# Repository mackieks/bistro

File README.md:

# bistro
Wii U regulator board. Runs a Wii U motherboard (no disc drive) from 1S lithium-ion. Licensed under Solderpad Hardware License v2.1. Have fun!

- x2 SiC431C 24A buck regulators for 1v and 1.15v (CPU + GPU)
- x2 MUN3CAD01-SB 1A bucks for 1.1V and 1.25V (for DRH)
- x1 MUN3CAD03-SE 3A buck for 1.5V (RAM)
- x1 TPS63810YFFR 2.5A buck-boost for 3.3V
- x1 FAN48610BUC50X 5V 1A boost (USB)

[Mouser project with BOM](https://www.mouser.com/ProjectManager/ProjectDetail.aspx?AccessID=d68b6111f5)

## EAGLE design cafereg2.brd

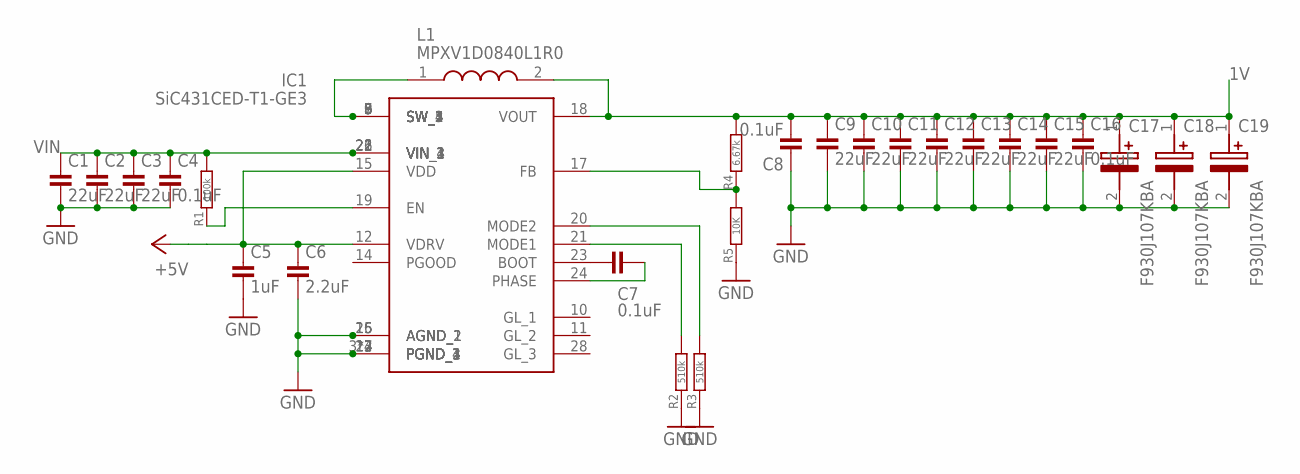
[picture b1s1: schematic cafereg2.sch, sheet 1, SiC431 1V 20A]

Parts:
C1, C2, C3, C9, C10, C11, C12, C13, C14, C15: 22uF; C0603
C4, C7, C8, C16: 0.1uF; C0402
C5: 1uF; C0402
C6: 2.2uF; C0402
C17, C18, C19: F930J107KBA; CAPPM3528X210N
IC1: SiC431CED-T1-GE3; SIC431AEDT1GE3
L1: MPXV1D0840L1R0; INDPM8680X400N
R1: 100k; R0402
R2, R3: 510k; R0402
R4: 6.67k; R0402
R5: 10K; R0402

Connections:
1V: C8.2, C9.1, C10.1, C11.1, C12.1, C13.1, C14.1, C15.1, C16.1, C17.1 (+), C18.1 (+), C19.1 (+), IC1.18 (VOUT), L1.2, R4.2
+5V: C5.1, C6.1, IC1.12 (VDRV), IC1.15 (VDD); also elsewhere on the board
BOOT: C7.1, IC1.23 (BOOT)
FB: IC1.17 (FB), R4.1, R5.2
GND: C1.2, C2.2, C3.2, C4.2, C5.2, C6.2, C8.1, C9.2, C10.2, C11.2, C12.2, C13.2, C14.2, C15.2, C16.2, C17.2 (-), C18.2 (-), C19.2 (-), IC1.3 (PGND_1), IC1.4 (PGND_2), IC1.13 (PGND_3), IC1.16 (AGND_1), IC1.25 (AGND_2), IC1.27 (PGND_4), IC1.29 (PGND_1), R2.1, R3.1, R5.1; also elsewhere on the board
unnamed: IC1.19 (EN), R1.1
unnamed: IC1.21 (MODE1), R2.2
unnamed: IC1.5 (SW_1), IC1.6 (SW_2), IC1.7 (SW_3), IC1.8 (SW_4), IC1.9 (SW_5), L1.1
unnamed: IC1.20 (MODE2), R3.2
PHASE: C7.2, IC1.24 (PHASE)
VIN: C1.1, C2.1, C3.1, C4.1, IC1.1 (VIN_1), IC1.2 (VIN_2), IC1.22 (VIN_3), IC1.26 (VIN_4), R1.2; also elsewhere on the board

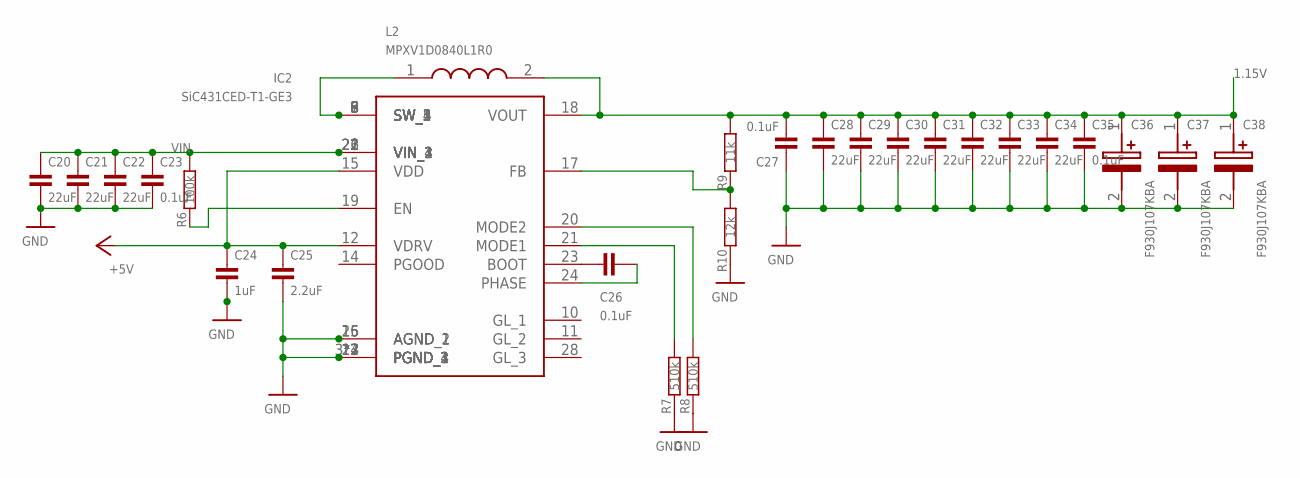
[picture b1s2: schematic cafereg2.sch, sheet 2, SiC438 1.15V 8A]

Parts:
C20, C21, C22, C28, C29, C30, C31, C32, C33, C34: 22uF; C0603
C23, C26, C27, C35: 0.1uF; C0402
C24: 1uF; C0402
C25: 2.2uF; C0402
C36, C37, C38: F930J107KBA; CAPPM3528X210N
IC2: SiC431CED-T1-GE3; SIC431AEDT1GE3
L2: MPXV1D0840L1R0; INDPM8680X400N
R6: 100k; R0402
R7, R8: 510k; R0402
R9: 11k; R0402
R10: 12k; R0402

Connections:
1.15V: C27.2, C28.1, C29.1, C30.1, C31.1, C32.1, C33.1, C34.1, C35.1, C36.1 (+), C37.1 (+), C38.1 (+), IC2.18 (VOUT), L2.2, R9.2
+5V: C24.1, C25.1, IC2.12 (VDRV), IC2.15 (VDD); also elsewhere on the board
BOOT2: C26.1, IC2.23 (BOOT)
FB2: IC2.17 (FB), R9.1, R10.2
GND: C20.2, C21.2, C22.2, C23.2, C24.2, C25.2, C27.1, C28.2, C29.2, C30.2, C31.2, C32.2, C33.2, C34.2, C35.2, C36.2 (-), C37.2 (-), C38.2 (-), IC2.3 (PGND_1), IC2.4 (PGND_2), IC2.13 (PGND_3), IC2.16 (AGND_1), IC2.25 (AGND_2), IC2.27 (PGND_4), IC2.29 (PGND_1), R7.1, R8.1, R10.1; also elsewhere on the board
unnamed: IC2.19 (EN), R6.1
unnamed: IC2.5 (SW_1), IC2.6 (SW_2), IC2.7 (SW_3), IC2.8 (SW_4), IC2.9 (SW_5), L2.1
unnamed: IC2.21 (MODE1), R7.2
unnamed: IC2.20 (MODE2), R8.2
PHASE2: C26.2, IC2.24 (PHASE)
VIN: C20.1, C21.1, C22.1, C23.1, IC2.1 (VIN_1), IC2.2 (VIN_2), IC2.22 (VIN_3), IC2.26 (VIN_4), R6.2; also elsewhere on the board

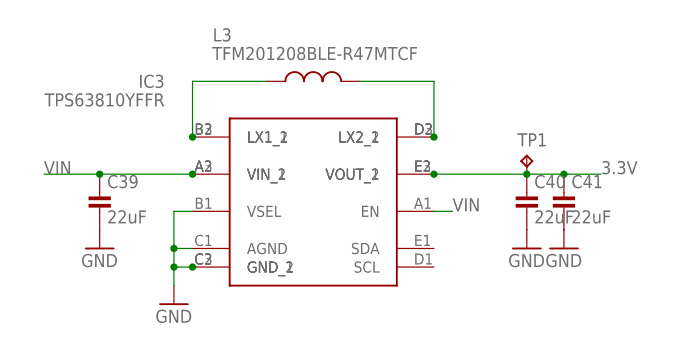
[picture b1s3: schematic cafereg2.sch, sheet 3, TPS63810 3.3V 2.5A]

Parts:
C39, C40, C41: 22uF; C0603
IC3: TPS63810YFFR; BGA15C40P3X5_134X226X62
L3: TFM201208BLE-R47MTCF; INDC2009X120
TP1: TPTP12SQ; TP12SQ

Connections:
3.3V: C40.1, C41.1, IC3.E2 (VOUT_1), IC3.E3 (VOUT_2), TP1.TP
GND: C39.2, C40.2, C41.2, IC3.B1 (VSEL), IC3.C1 (AGND), IC3.C2 (GND_1), IC3.C3 (GND_2); also elsewhere on the board
SW1: IC3.B2 (LX1_1), IC3.B3 (LX1_2), L3.1
SW2: IC3.D2 (LX2_1), IC3.D3 (LX2_2), L3.2
VIN: C39.1, IC3.A1 (EN), IC3.A2 (VIN_1), IC3.A3 (VIN_2); also elsewhere on the board

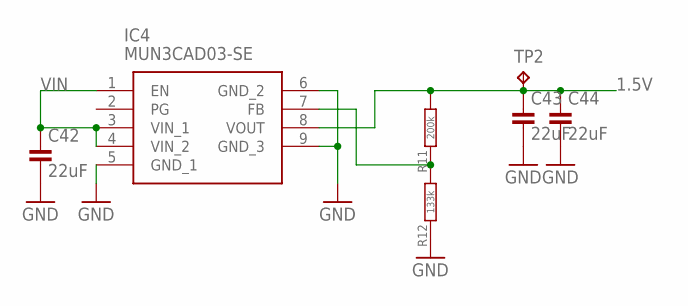
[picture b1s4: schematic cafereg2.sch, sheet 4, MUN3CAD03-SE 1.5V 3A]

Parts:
C42, C43, C44: 22uF; C0603
IC4: MUN3CAD03-SE; MUN3CAD03SE
R11: 200k; R0402
R12: 133k; R0402
TP2: TPTP12SQ; TP12SQ

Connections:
1.5V: C43.1, C44.1, IC4.8 (VOUT), R11.2, TP2.TP
FB1: IC4.7 (FB), R11.1, R12.2
GND: C42.2, C43.2, C44.2, IC4.5 (GND_1), IC4.6 (GND_2), IC4.9 (GND_3), R12.1; also elsewhere on the board
VIN: C42.1, IC4.1 (EN), IC4.3 (VIN_1), IC4.4 (VIN_2); also elsewhere on the board

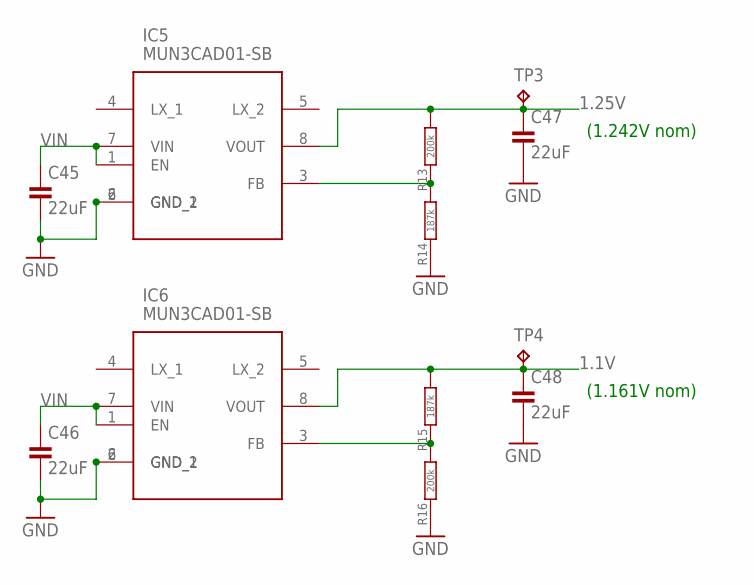
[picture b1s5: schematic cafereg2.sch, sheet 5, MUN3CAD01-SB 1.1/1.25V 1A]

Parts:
C45, C46, C47, C48: 22uF; C0603
IC5, IC6: MUN3CAD01-SB; MUN3CAD01SB
R13, R16: 200k; R0402
R14, R15: 187k; R0402
TP3, TP4: TPTP12SQ; TP12SQ

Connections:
1.1V: C48.1, IC6.8 (VOUT), R15.2, TP4.TP
1.25V: C47.1, IC5.8 (VOUT), R13.2, TP3.TP
GND: C45.2, C46.2, C47.2, C48.2, IC5.2 (GND_1), IC5.6 (GND_2), IC6.2 (GND_1), IC6.6 (GND_2), R14.1, R16.1; also elsewhere on the board
unnamed: IC6.3 (FB), R15.1, R16.2
unnamed: IC5.3 (FB), R13.1, R14.2
VIN: C45.1, C46.1, IC5.1 (EN), IC5.7 (VIN), IC6.1 (EN), IC6.7 (VIN); also elsewhere on the board

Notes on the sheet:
(1.161V nom)
(1.242V nom)

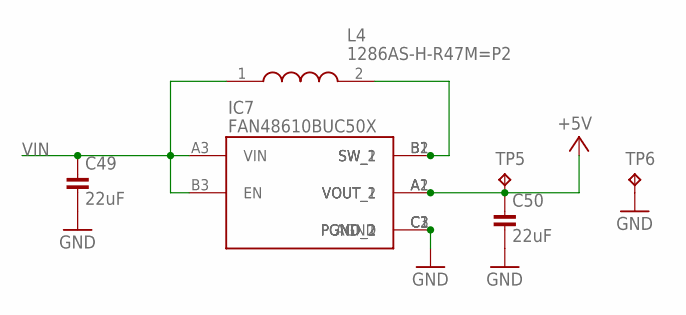
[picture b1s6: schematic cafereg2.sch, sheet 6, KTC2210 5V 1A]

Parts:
C49, C50: 22uF; C0603
IC7: FAN48610BUC50X; BGA9C40P3X3_122X122X62
L4: 1286AS-H-R47M=P2; 1286ASH1R0MP2
TP5, TP6: TPTP12SQ; TP12SQ

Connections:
+5V: C50.1, IC7.A1 (VOUT_1), IC7.A2 (VOUT_2), TP5.TP; also elsewhere on the board
GND: C49.2, C50.2, IC7.C1 (PGND_1), IC7.C2 (PGND_2), IC7.C3 (AGND), TP6.TP; also elsewhere on the board
SW: IC7.B1 (SW_1), IC7.B2 (SW_2), L4.2
VIN: C49.1, IC7.A3 (VIN), IC7.B3 (EN), L4.1; also elsewhere on the board

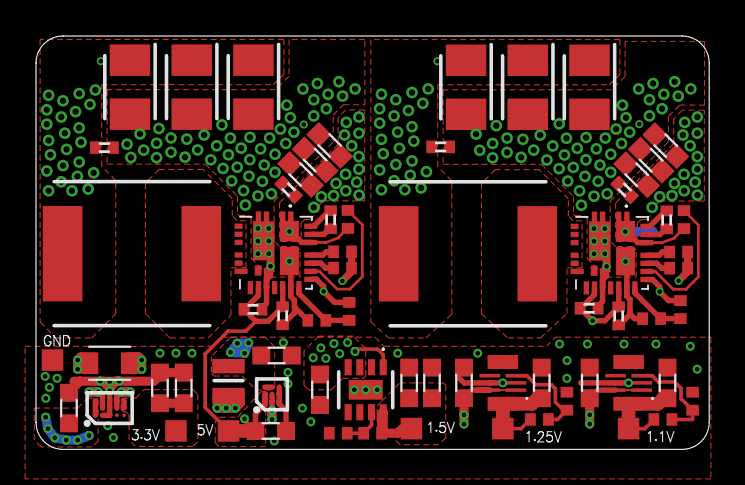
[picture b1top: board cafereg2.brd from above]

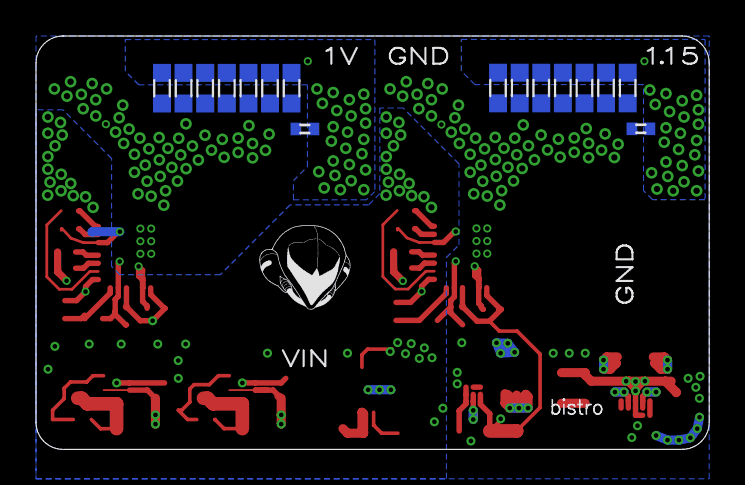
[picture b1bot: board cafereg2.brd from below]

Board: 4 copper layers, 37.4 x 23.0 mm, 83 parts (16 on the bottom side), 29 nets.

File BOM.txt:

Partlist

Exported from cafereg2.sch at 12/10/2023 4:18 PM

EAGLE Version 9.6.1 Copyright (c) 1988-2020 Autodesk, Inc.

Assembly variant: 

Part     Value                Device                   Package                 Library        Sheet

C1       22uF                 C-USC0603                C0603                   resistor       1
C2       22uF                 C-USC0603                C0603                   resistor       1
C3       22uF                 C-USC0603                C0603                   resistor       1
C4       0.1uF                C-USC0402                C0402                   resistor       1
C5       1uF                  C-USC0402                C0402                   resistor       1
C6       2.2uF                C-USC0402                C0402                   resistor       1
C7       0.1uF                C-USC0402                C0402                   resistor       1
C8       0.1uF                C-USC0402                C0402                   resistor       1
C9       22uF                 C-USC0603                C0603                   resistor       1
C10      22uF                 C-USC0603                C0603                   resistor       1
C11      22uF                 C-USC0603                C0603                   resistor       1
C12      22uF                 C-USC0603                C0603                   resistor       1
C13      22uF                 C-USC0603                C0603                   resistor       1
C14      22uF                 C-USC0603                C0603                   resistor       1
C15      22uF                 C-USC0603                C0603                   resistor       1
C16      0.1uF                C-USC0402                C0402                   resistor       1
C17      F930J107KBA          F930J107KBA              CAPPM3528X210N          SamacSys_Parts 1
C18      F930J107KBA          F930J107KBA              CAPPM3528X210N          SamacSys_Parts 1
C19      F930J107KBA          F930J107KBA              CAPPM3528X210N          SamacSys_Parts 1
C20      22uF                 C-USC0603                C0603                   resistor       2
C21      22uF                 C-USC0603                C0603                   resistor       2
C22      22uF                 C-USC0603                C0603                   resistor       2
C23      0.1uF                C-USC0402                C0402                   resistor       2
C24      1uF                  C-USC0402                C0402                   resistor       2
C25      2.2uF                C-USC0402                C0402                   resistor       2
C26      0.1uF                C-USC0402                C0402                   resistor       2
C27      0.1uF                C-USC0402                C0402                   resistor       2
C28      22uF                 C-USC0603                C0603                   resistor       2
C29      22uF                 C-USC0603                C0603                   resistor       2
C30      22uF                 C-USC0603                C0603                   resistor       2
C31      22uF                 C-USC0603                C0603                   resistor       2
C32      22uF                 C-USC0603                C0603                   resistor       2
C33      22uF                 C-USC0603                C0603                   resistor       2
C34      22uF                 C-USC0603                C0603                   resistor       2
C35      0.1uF                C-USC0402                C0402                   resistor       2
C36      F930J107KBA          F930J107KBA              CAPPM3528X210N          SamacSys_Parts 2
C37      F930J107KBA          F930J107KBA              CAPPM3528X210N          SamacSys_Parts 2
C38      F930J107KBA          F930J107KBA              CAPPM3528X210N          SamacSys_Parts 2
C39      22uF                 C-USC0603                C0603                   resistor       3
C40      22uF                 C-USC0603                C0603                   resistor       3
C41      22uF                 C-USC0603                C0603                   resistor       3
C42      22uF                 C-USC0603                C0603                   resistor       4
C43      22uF                 C-USC0603                C0603                   resistor       4
C44      22uF                 C-USC0603                C0603                   resistor       4
C45      22uF                 C-USC0603                C0603                   resistor       5
C46      22uF                 C-USC0603                C0603                   resistor       5
C47      22uF                 C-USC0603                C0603                   resistor       5
C48      22uF                 C-USC0603                C0603                   resistor       5
C49      22uF                 C-USC0603                C0603                   resistor       6
C50      22uF                 C-USC0603                C0603                   resistor       6
IC1      SiC431CED-T1-GE3     SiC431CED-T1-GE3         SiC431CED-T1-GE3        personal       1
IC2      SiC431CED-T1-GE3     SiC431CED-T1-GE3         SiC431CED-T1-GE3        personal       2
IC3      TPS63810YFFR         TPS63810YFFR             BGA15C40P3X5_134X226X62 SamacSys_Parts 3
IC4      MUN3CAD03-SE         MUN3CAD03-SE             MUN3CAD03SE             SamacSys_Parts 4
IC5      MUN3CAD01-SB         MUN3CAD01-SB             MUN3CAD01SB             SamacSys_Parts 5
IC6      MUN3CAD01-SB         MUN3CAD01-SB             MUN3CAD01SB             SamacSys_Parts 5
IC7      FAN48610BUC50X       FAN48610BUC50X           BGA9C40P3X3_122X122X62  SamacSys_Parts 6
L1       MPXV1D0840L1R0       MPXV1D0840L1R0           INDPM8680X400N          SamacSys_Parts 1
L2       MPXV1D0840L1R0       MPXV1D0840L1R0           INDPM8680X400N          SamacSys_Parts 2
L3       TFM201208BLE-R47MTCF L_CHIP-0805(2012-METRIC) INDC2009X120            Inductor       3
L4       1286AS-H-R47M=P2     1286AS-H-R47M=P2         1286ASH1R0MP2           SamacSys_Parts 6
R1       100k                 R-US_R0402               R0402                   resistor       1
R2       510k                 R-US_R0402               R0402                   resistor       1
R3       510k                 R-US_R0402               R0402                   resistor       1
R4       6.67k                R-US_R0402               R0402                   resistor       1
R5       10K                  R-US_R0402               R0402                   resistor       1
R6       100k                 R-US_R0402               R0402                   resistor       2
R7       510k                 R-US_R0402               R0402                   resistor       2
R8       510k                 R-US_R0402               R0402                   resistor       2
R9       11k                  R-US_R0402               R0402                   resistor       2
R10      12k                  R-US_R0402               R0402                   resistor       2
R11      200k                 R-US_R0402               R0402                   resistor       4
R12      133k                 R-US_R0402               R0402                   resistor       4
R13      200k                 R-US_R0402               R0402                   resistor       5
R14      187k                 R-US_R0402               R0402                   resistor       5
R15      187k                 R-US_R0402               R0402                   resistor       5
R16      200k                 R-US_R0402               R0402                   resistor       5

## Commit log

2023-09-17 add board pics
2023-09-17 add files
2023-12-10 update bom
2024-01-23 change to solderpad license
2024-03-21 update iBOM
2025-01-14 Update Mouser project link
